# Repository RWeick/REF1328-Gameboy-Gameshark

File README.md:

# REF1328-Gameboy-Gameshark
The Kicad files and ROM dump of one hardware variant of the Gameboy Gameshark

PCB Thickness: 0.8 mm

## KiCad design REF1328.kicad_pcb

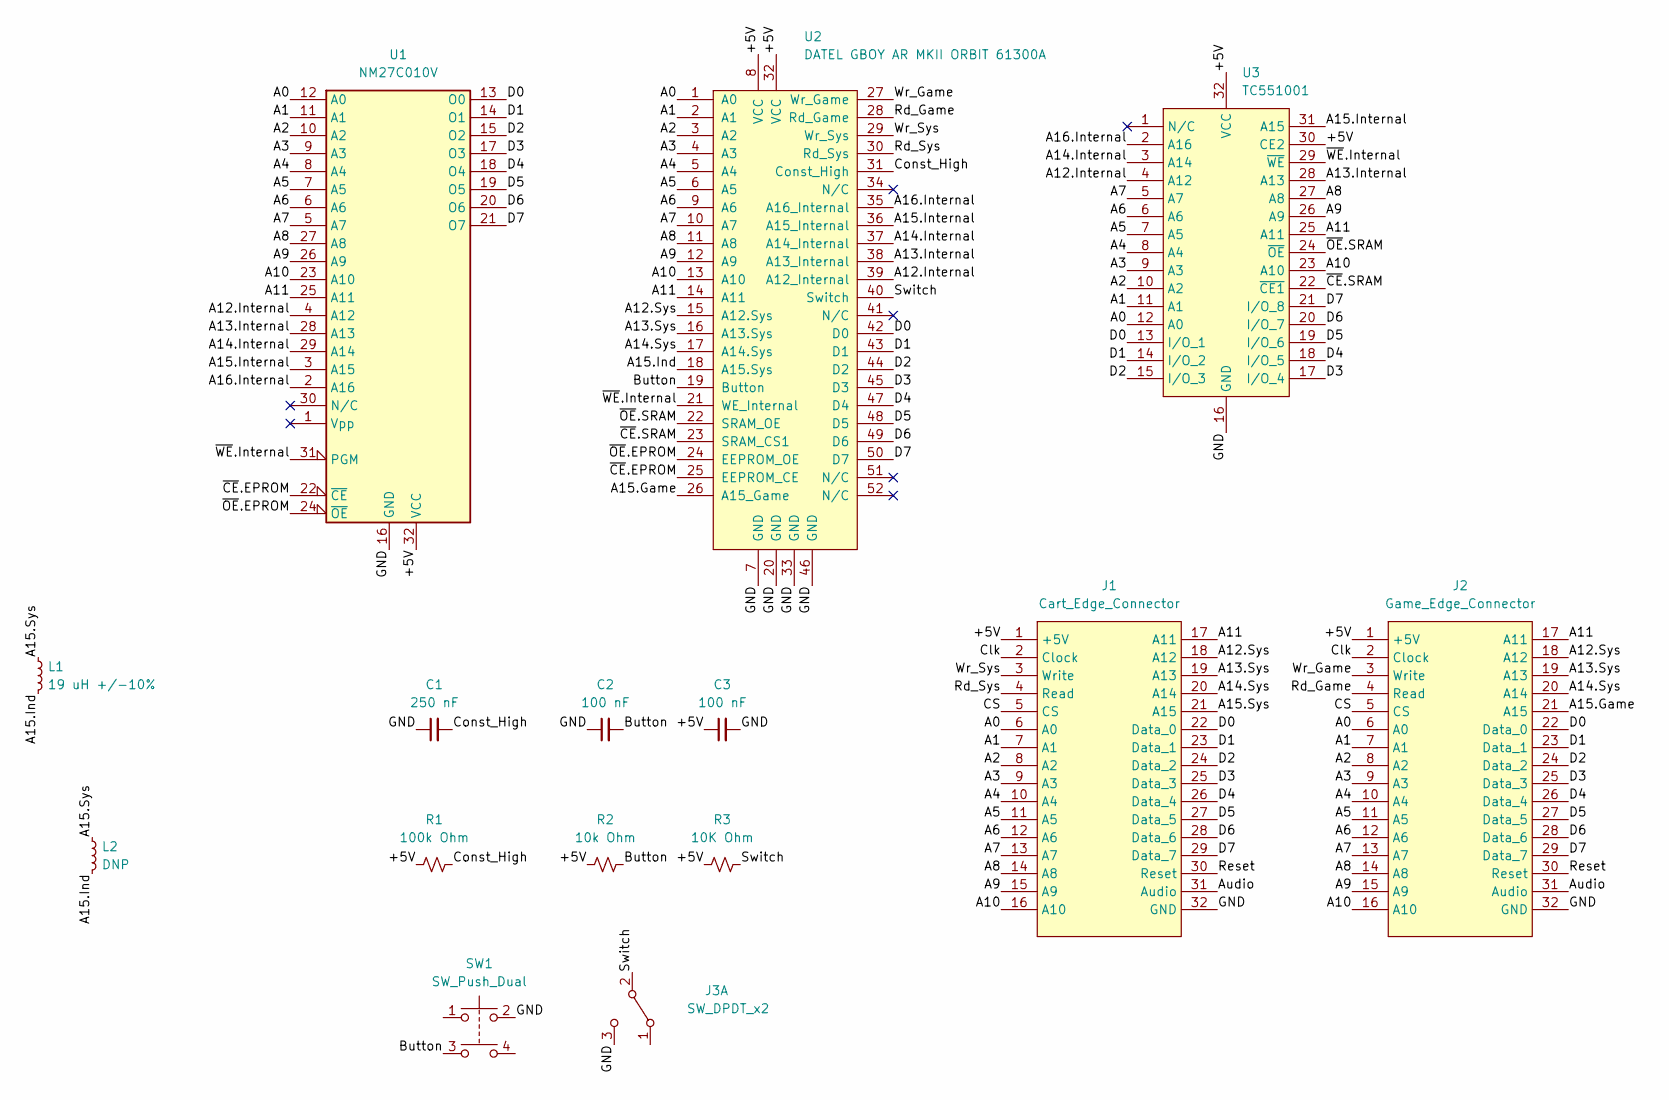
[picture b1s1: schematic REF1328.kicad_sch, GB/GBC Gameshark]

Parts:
C1: 250 nF; Capacitor
C2, C3: 100 nF; Capacitor
J1: Cart_Edge_Connector; Cart Edge Connector
J2: Game_Edge_Connector; Game Connector
J3: SW_DPDT_x2; Switch
L1: 19 uH +/-10%; THT Inductor
L2: DNP; Capacitor
R1: 100k Ohm; Capacitor
R2: 10k Ohm; Capacitor
R3: 10K Ohm; Capacitor
SW1: SW_Push_Dual; Button
U1: NM27C010V
U2: DATEL GBOY AR MKII ORBIT 61300A
U3: TC551001

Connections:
/+5V: C3.1, J1.1 (+5V), J2.1 (+5V), R1.1, R2.1, R3.1, U1.32 (VCC), U2.8 (VCC), U2.32 (VCC), U3.30 (CE2), U3.32 (VCC)
/A0: J1.6 (A0), J2.6 (A0), U1.12 (A0), U2.1 (A0), U3.12 (A0)
/A1: J1.7 (A1), J2.7 (A1), U1.11 (A1), U2.2 (A1), U3.11 (A1)
/A2: J1.8 (A2), J2.8 (A2), U1.10 (A2), U2.3 (A2), U3.10 (A2)
/A3: J1.9 (A3), J2.9 (A3), U1.9 (A3), U2.4 (A3), U3.9 (A3)
/A4: J1.10 (A4), J2.10 (A4), U1.8 (A4), U2.5 (A4), U3.8 (A4)
/A5: J1.11 (A5), J2.11 (A5), U1.7 (A5), U2.6 (A5), U3.7 (A5)
/A6: J1.12 (A6), J2.12 (A6), U1.6 (A6), U2.9 (A6), U3.6 (A6)
/A7: J1.13 (A7), J2.13 (A7), U1.5 (A7), U2.10 (A7), U3.5 (A7)
/A8: J1.14 (A8), J2.14 (A8), U1.27 (A8), U2.11 (A8), U3.27 (A8)
/A9: J1.15 (A9), J2.15 (A9), U1.26 (A9), U2.12 (A9), U3.26 (A9)
/A10: J1.16 (A10), J2.16 (A10), U1.23 (A10), U2.13 (A10), U3.23 (A10)
/A11: J1.17 (A11), J2.17 (A11), U1.25 (A11), U2.14 (A11), U3.25 (A11)
/A12.Internal: U1.4 (A12), U2.39 (A12_Internal), U3.4 (A12)
/A12.Sys: J1.18 (A12), J2.18 (A12), U2.15 (A12.Sys)
/A13.Internal: U1.28 (A13), U2.38 (A13_Internal), U3.28 (A13)
/A13.Sys: J1.19 (A13), J2.19 (A13), U2.16 (A13.Sys)
/A14.Internal: U1.29 (A14), U2.37 (A14_Internal), U3.3 (A14)
/A14.Sys: J1.20 (A14), J2.20 (A14), U2.17 (A14.Sys)
/A15.Game: J2.21 (A15), U2.26 (A15_Game)
/A15.Ind: L1.2, L2.2, U2.18 (A15.Sys)
/A15.Internal: U1.3 (A15), U2.36 (A15_Internal), U3.31 (A15)
/A15.Sys: J1.21 (A15), L1.1, L2.1
/A16.Internal: U1.2 (A16), U2.35 (A16_Internal), U3.2 (A16)
/Audio: J1.31 (Audio), J2.31 (Audio)
/Button: C2.2, R2.2, SW1.3, U2.19 (Button)
/CS: J1.5 (CS), J2.5 (CS)
/Clk: J1.2 (Clock), J2.2 (Clock)
/Const_High: C1.2, R1.2, U2.31 (Const_High)
/D0: J1.22 (Data_0), J2.22 (Data_0), U1.13 (O0), U2.42 (D0), U3.13 (I/O_1)
/D1: J1.23 (Data_1), J2.23 (Data_1), U1.14 (O1), U2.43 (D1), U3.14 (I/O_2)
/D2: J1.24 (Data_2), J2.24 (Data_2), U1.15 (O2), U2.44 (D2), U3.15 (I/O_3)
/D3: J1.25 (Data_3), J2.25 (Data_3), U1.17 (O3), U2.45 (D3), U3.17 (I/O_4)
/D4: J1.26 (Data_4), J2.26 (Data_4), U1.18 (O4), U2.47 (D4), U3.18 (I/O_5)
/D5: J1.27 (Data_5), J2.27 (Data_5), U1.19 (O5), U2.48 (D5), U3.19 (I/O_6)
/D6: J1.28 (Data_6), J2.28 (Data_6), U1.20 (O6), U2.49 (D6), U3.20 (I/O_7)
/D7: J1.29 (Data_7), J2.29 (Data_7), U1.21 (O7), U2.50 (D7), U3.21 (I/O_8)
/GND: C1.1, C2.1, C3.2, J1.32 (GND), J2.32 (GND), J3.3 (C), J3.4 (A), SW1.2, U1.16 (GND), U2.7 (GND), U2.20 (GND), U2.33 (GND), U2.46 (GND), U3.16 (GND)
/Rd_Game: J2.4 (Read), U2.28 (Rd_Game)
/Rd_Sys: J1.4 (Read), U2.30 (Rd_Sys)
/Reset: J1.30 (Reset), J2.30 (Reset)
/Switch: J3.2 (B), R3.2, U2.40 (Switch)
/Wr_Game: J2.3 (Write), U2.27 (Wr_Game)
/Wr_Sys: J1.3 (Write), U2.29 (Wr_Sys)
/~CE.EPROM: U1.22 (~CE), U2.25 (EEPROM_CE)
/~CE.SRAM: U2.23 (SRAM_CS1), U3.22 (~CE1)
/~OE.EPROM: U1.24 (~OE), U2.24 (EEPROM_OE)
/~OE.SRAM: U2.22 (SRAM_OE), U3.24 (~OE)
/~WE.Internal: U1.31 (PGM), U2.21 (WE_Internal), U3.29 (~WE)

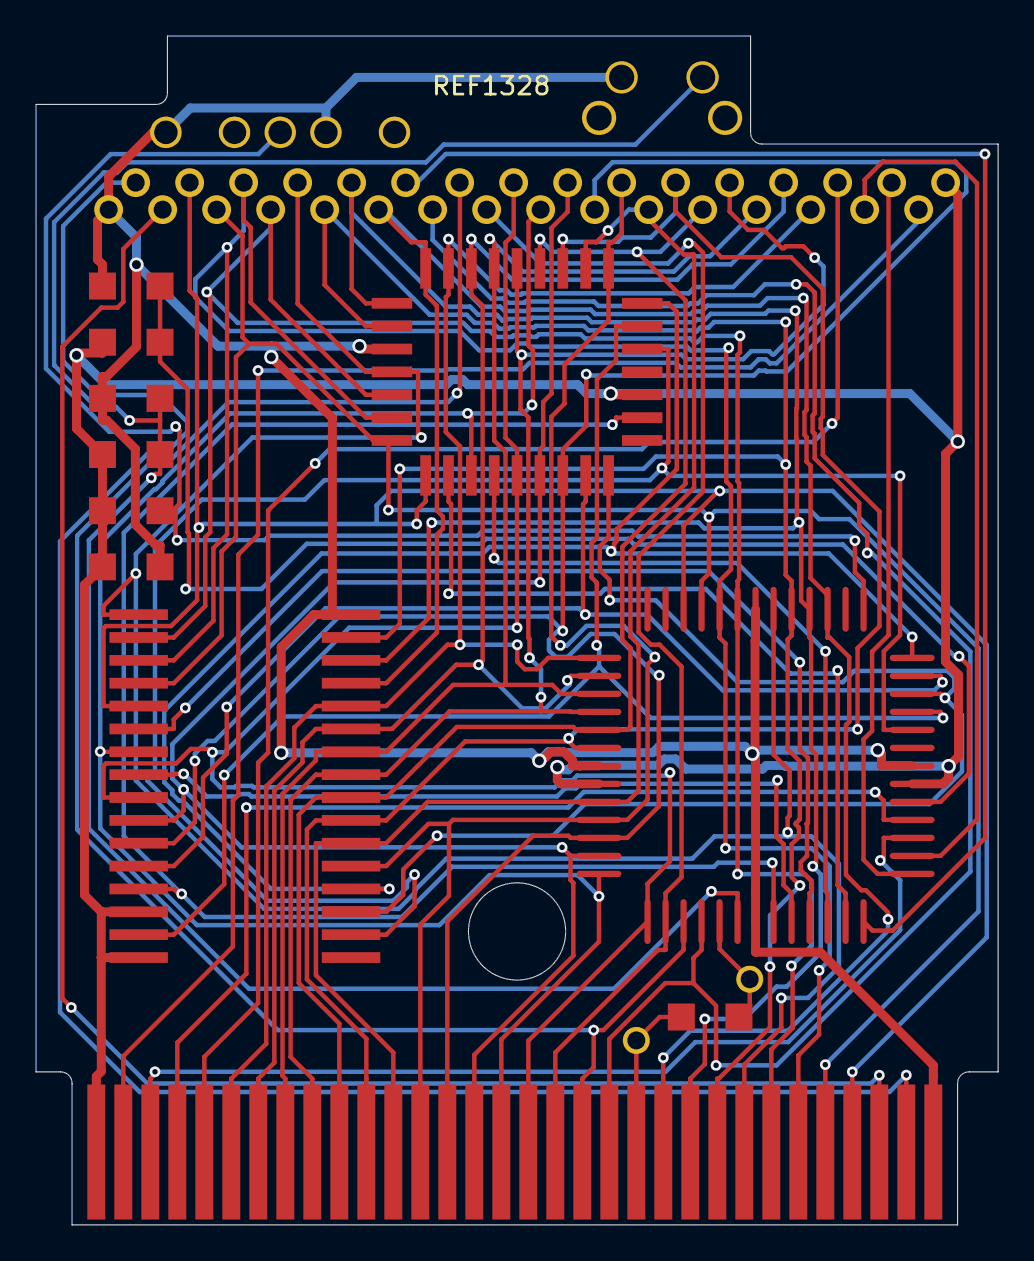
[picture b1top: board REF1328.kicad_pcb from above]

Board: 2 copper layers, 53.4 x 66.0 mm, 15 parts (0 on the bottom side), 49 nets.
